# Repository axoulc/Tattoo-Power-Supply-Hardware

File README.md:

# Tattoo Power Supply Hardware

This is an open source project for a tattoo power supply circuit board. The circuit board is designed to provide power to tattoo machines, allowing artists to control the voltage and frequency of their machines for precise and consistent results.

# Features

- Dual channel power supply
- Each channel can provide up to 20V and 3A
- 1 footswitch input and 1 handswitch input
- Adjustable voltage and frequency controls
- Compatible with most tattoo machines
- OLED display for easy monitoring of voltage and frequency
- Overload protection for safety
- USB-C Power Delivery up to 100W
- DC Jack input up to 24V

# Getting Started

## PCB

To get started with this project, you will need at least KiCAD 7. You can download KiCAD from the [KiCAD website](https://kicad.org/). You will find gerber files in each release, which you can use to order PCBs from a PCB manufacturer. Every files will be available in the PCB folder. For components, you can use the BOM file to order them from a distributor `Tattoo_Supply_bom_Vx.x.csv`.

## Case

The case is designed with FreeCAD. In `Case` folder, you will find `.FCStd` files which are source files for FreeCAD and `.3mf` files which are 3D printer ready. The shapes of the case are very simple, if you're 3D designer, make it prettier !

# License

This project is licensed under the CERN Open Hardware Licence Version 2 - Permissive. See the LICENSE file for more information.

# Contact

If you have any questions or feedback about this project, please feel free to contact the project maintainer in issue section.

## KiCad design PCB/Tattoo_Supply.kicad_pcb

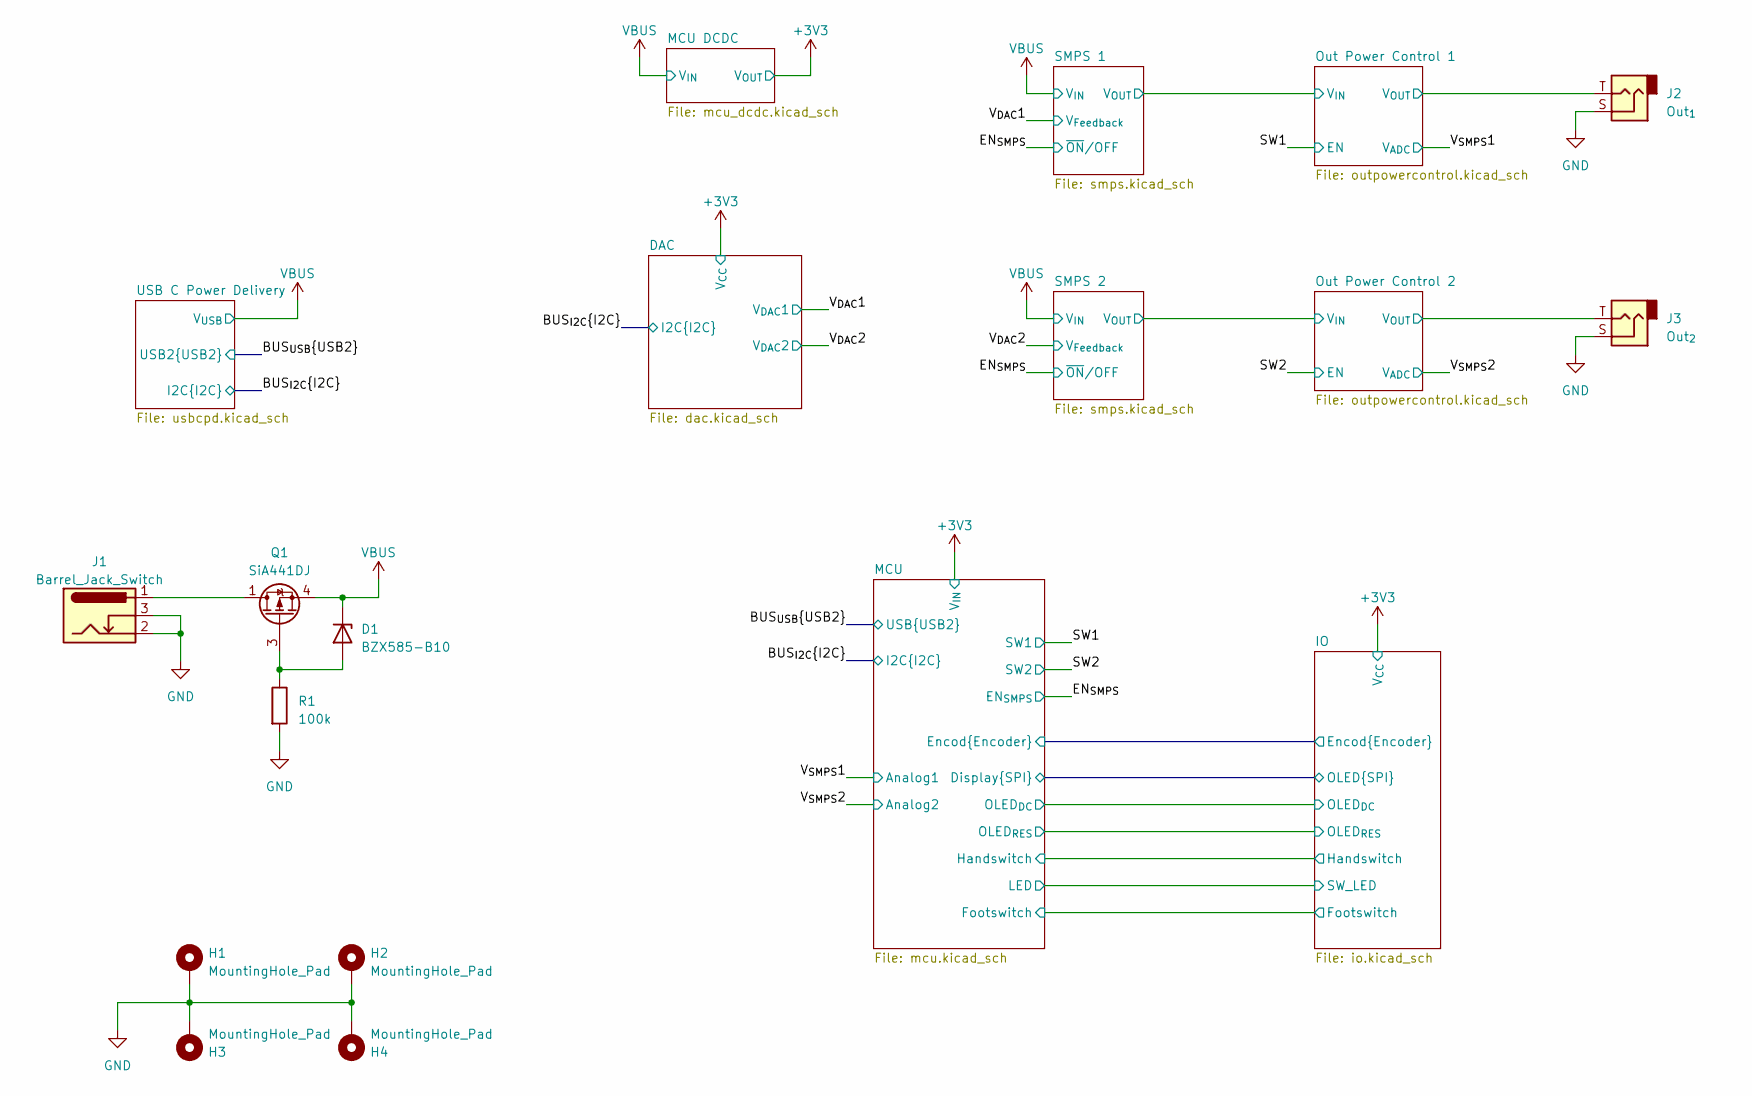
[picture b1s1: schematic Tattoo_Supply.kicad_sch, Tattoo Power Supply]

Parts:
D1: BZX585-B10; D_SOD-523; MPN BZX585-B10,135
H1, H2, H3, H4: MountingHole_Pad; MountingHole_2.7mm_M2.5_DIN965_Pad
J1: Barrel_Jack_Switch; BarrelJack_CUI_PJ-102AH_Horizontal; MPN PJ-102A
J2: Out_{1}; MJ63022A; MPN MJ-63022A
J3: Out_{2}; MJ63022A; MPN MJ-63022A
Q1: SiA441DJ; Vishay_PowerPAK_SC70-6L_Single; MPN SIA441DJ-T1-GE3
R1: 100k; R_0603_1608Metric; MPN ERJ-3EKF1003V

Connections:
/Out Power Control 1/V_{OUT}: J2.T; also elsewhere on the board
/Out Power Control 2/V_{OUT}: J3.T; also elsewhere on the board
GND: H1.1, H2.1, H3.1, H4.1, J1.2, J1.3, J2.S, J3.S, R1.2; also elsewhere on the board
unnamed: D1.2 (A), Q1.3 (G), R1.1
unnamed: J1.1, Q1.1 (D)
VBUS: D1.1 (K), Q1.4 (S); also elsewhere on the board

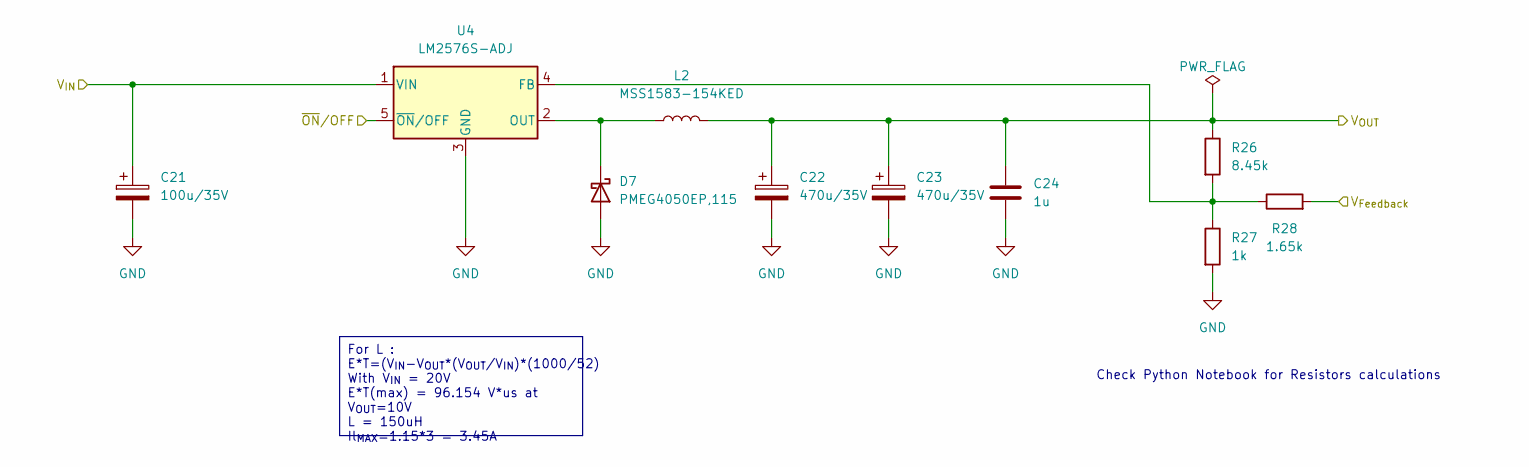
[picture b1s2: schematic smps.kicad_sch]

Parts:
C21: 100u/35V; CP_Elec_6.3x7.7; MPN 865080545012
C22, C23: 470u/35V; CP_Elec_8x10; MPN EMZS350ARA471MHA0G
C24: 1u; C_0603_1608Metric; MPN CGA3E1X7R1V105K080AC
D7: PMEG4050EP,115; D_SOD-128; MPN PMEG4050EP,115
L2: MSS1583-154KED; MSS1583; MPN MSS1583-154KED
R26: 8.45k; R_0603_1608Metric; MPN ERJ-3EKF8451V
R27: 1k; R_0603_1608Metric; MPN ERJ-3EKF1001V
R28: 1.65k; R_0603_1608Metric; MPN ERJ-3EKF1651V
U4: LM2576S-ADJ; TO-263-5_TabPin3; MPN LM2576D2T-ADJR4G

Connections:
/EN_{SMPS}: U4.5 (~ON/OFF); also elsewhere on the board
/Out Power Control 1/V_{IN}: C22.1, C23.1, C24.1, L2.2, R26.1; also elsewhere on the board
/V_{DAC}1: R28.2; also elsewhere on the board
GND: C21.2, C22.2, C23.2, C24.2, D7.2 (A), R27.2, U4.3 (GND); also elsewhere on the board
unnamed: D7.1 (K), L2.1, U4.2 (OUT)
unnamed: R26.2, R27.1, R28.1, U4.4 (FB)
VBUS: C21.1, U4.1 (VIN); also elsewhere on the board

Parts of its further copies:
C7: 100u/35V; CP_Elec_6.3x7.7; MPN 865080545012
C8, C9: 470u/35V; CP_Elec_8x10; MPN EMZS350ARA471MHA0G
C10: 1u; C_0603_1608Metric; MPN CGA3E1X7R1V105K080AC
D6: PMEG4050EP,115; D_SOD-128; MPN PMEG4050EP,115
L1: MSS1583-154KED; MSS1583; MPN MSS1583-154KED
R13: 8.45k; R_0603_1608Metric; MPN ERJ-3EKF8451V
R14: 1k; R_0603_1608Metric; MPN ERJ-3EKF1001V
R15: 1.65k; R_0603_1608Metric; MPN ERJ-3EKF1651V
U2: LM2576S-ADJ; TO-263-5_TabPin3; MPN LM2576D2T-ADJR4G

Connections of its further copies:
/EN_{SMPS}: U2.5 (~ON/OFF); also elsewhere on the board
/Out Power Control 2/V_{IN}: C8.1, C9.1, C10.1, L1.2, R13.1; also elsewhere on the board
/V_{DAC}2: R15.2; also elsewhere on the board
GND: C7.2, C8.2, C9.2, C10.2, D6.2 (A), R14.2, U2.3 (GND); also elsewhere on the board
unnamed: D6.1 (K), L1.1, U2.2 (OUT)
unnamed: R13.2, R14.1, R15.1, U2.4 (FB)
VBUS: C7.1, U2.1 (VIN); also elsewhere on the board

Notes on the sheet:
For L : E*T=(V_{IN}-V_{OUT}*(V_{OUT}/V_{IN})*(1000/52) With V_{IN} = 20V E*T(max) = 96.154 V*us at V_{OUT}=10V L = 150uH Il_{MAX}=1.15*3 = 3.45A
Check Python Notebook for Resistors calculations

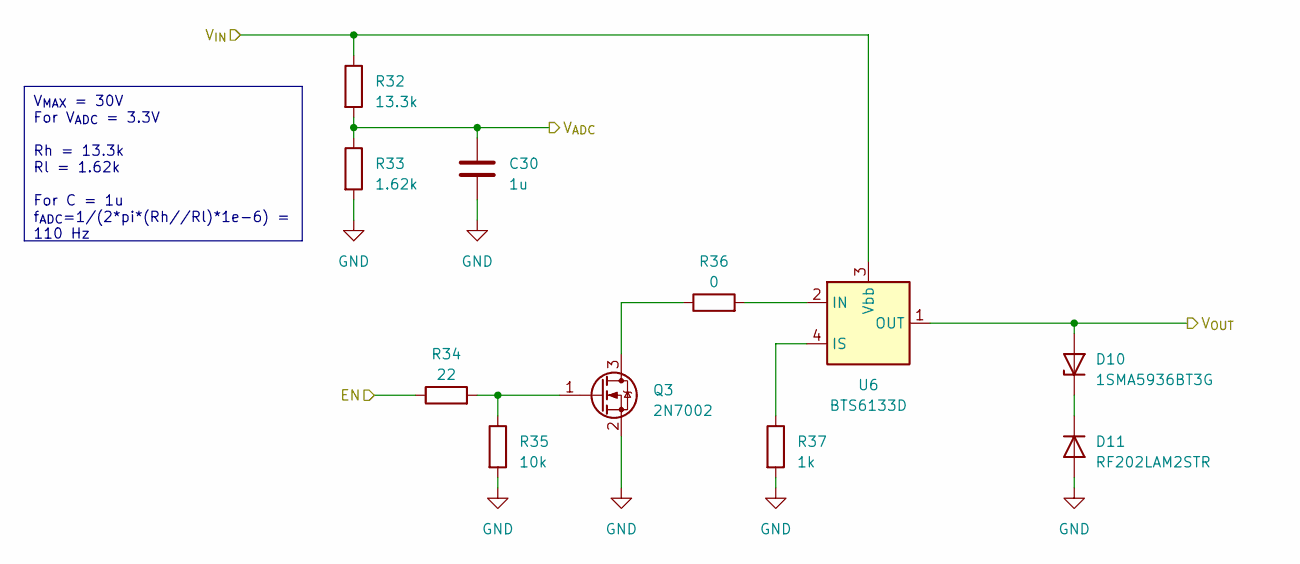
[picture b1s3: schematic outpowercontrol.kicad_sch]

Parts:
C30: 1u; C_0603_1608Metric; MPN CGA3E1X7R1V105K080AC
D10: 1SMA5936BT3G; D_SMA; MPN 1SMA5936BT3G
D11: RF202LAM2STR; D_SOD-128; MPN RF202LAM2STR
Q3: 2N7002; SOT-23; MPN 2N7002NXAKR
R32: 13.3k; R_0603_1608Metric; MPN ERJ-3EKF1332V
R33: 1.62k; R_0603_1608Metric; MPN ERJ-3EKF1621V
R34: 22; R_0603_1608Metric; MPN ERJ-3EKF22R0V
R35: 10k; R_0603_1608Metric; MPN ERJ-3EKF1002V
R36: 0; R_0603_1608Metric; MPN ERJ-3GEY0R00V
R37: 1k; R_0603_1608Metric; MPN ERJ-3EKF1001V
U6: BTS6133D; TO-252-4; MPN BTS6133D

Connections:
/Out Power Control 1/V_{IN}: R32.1, U6.3 (Vbb); also elsewhere on the board
/Out Power Control 1/V_{OUT}: D10.2 (A), U6.1 (OUT), U6.5 (OUT); also elsewhere on the board
/SW1: R34.1; also elsewhere on the board
/V_{SMPS}1: C30.1, R32.2, R33.1; also elsewhere on the board
GND: C30.2, D11.2 (A), Q3.2 (S), R33.2, R35.2, R37.2; also elsewhere on the board
unnamed: D10.1 (K), D11.1 (K)
unnamed: Q3.3 (D), R36.1
unnamed: Q3.1 (G), R34.2, R35.1
unnamed: R36.2, U6.2 (IN)
unnamed: R37.1, U6.4 (IS)

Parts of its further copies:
C34: 1u; C_0603_1608Metric; MPN CGA3E1X7R1V105K080AC
D12: 1SMA5936BT3G; D_SMA; MPN 1SMA5936BT3G
D13: RF202LAM2STR; D_SOD-128; MPN RF202LAM2STR
Q4: 2N7002; SOT-23; MPN 2N7002NXAKR
R42: 13.3k; R_0603_1608Metric; MPN ERJ-3EKF1332V
R43: 1.62k; R_0603_1608Metric; MPN ERJ-3EKF1621V
R44: 22; R_0603_1608Metric; MPN ERJ-3EKF22R0V
R45: 10k; R_0603_1608Metric; MPN ERJ-3EKF1002V
R46: 0; R_0603_1608Metric; MPN ERJ-3GEY0R00V
R47: 1k; R_0603_1608Metric; MPN ERJ-3EKF1001V
U8: BTS6133D; TO-252-4; MPN BTS6133D

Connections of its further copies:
/Out Power Control 2/V_{IN}: R42.1, U8.3 (Vbb); also elsewhere on the board
/Out Power Control 2/V_{OUT}: D12.2 (A), U8.1 (OUT), U8.5 (OUT); also elsewhere on the board
/SW2: R44.1; also elsewhere on the board
/V_{SMPS}2: C34.1, R42.2, R43.1; also elsewhere on the board
GND: C34.2, D13.2 (A), Q4.2 (S), R43.2, R45.2, R47.2; also elsewhere on the board
unnamed: D12.1 (K), D13.1 (K)
unnamed: Q4.3 (D), R46.1
unnamed: Q4.1 (G), R44.2, R45.1
unnamed: R46.2, U8.2 (IN)
unnamed: R47.1, U8.4 (IS)

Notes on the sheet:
V_{MAX} = 30V For V_{ADC} = 3.3V Rh = 13.3k Rl = 1.62k For C = 1u f_{ADC}=1/(2*pi*(Rh//Rl)*1e-6) = 110 Hz

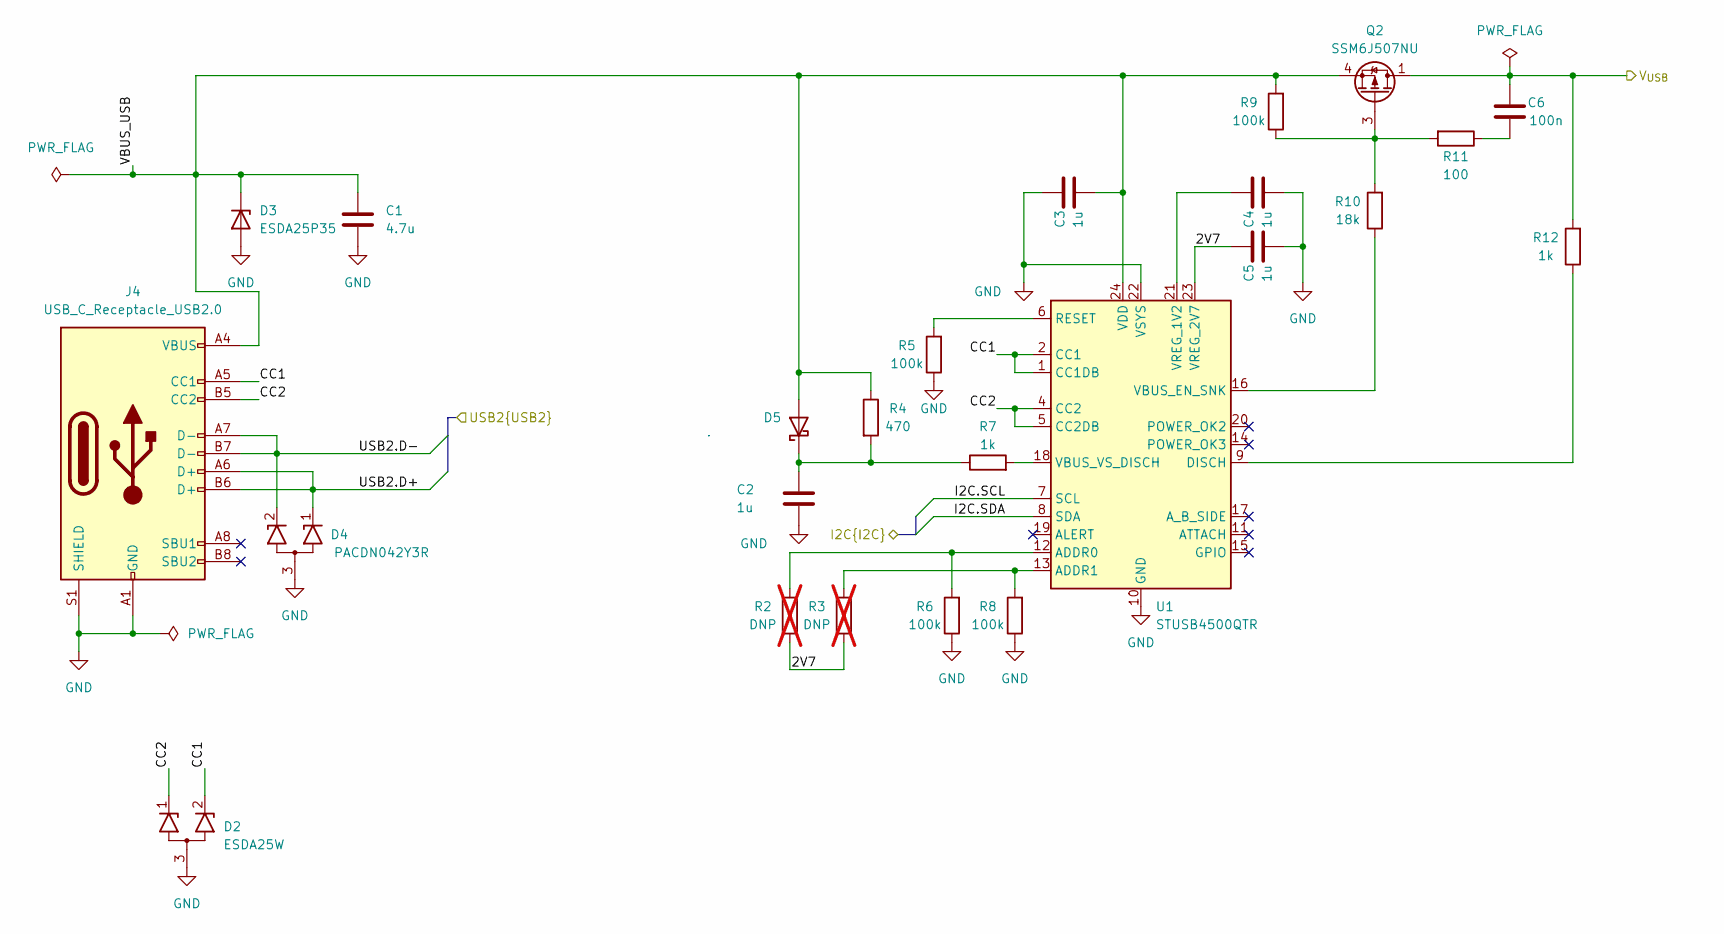
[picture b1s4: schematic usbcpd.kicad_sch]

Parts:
C1: 4.7u; C_0805_2012Metric; MPN GRM219R6YA475KA73D
C2, C3, C4, C5: 1u; C_0603_1608Metric; MPN CGA3E1X7R1V105K080AC
C6: 100n; C_0603_1608Metric; MPN CGA3E2X7R1H104M080AA
D2: ESDA25W; SOT-323_SC-70; MPN ESDA25W
D3: ESDA25P35; D_0603_1608Metric; MPN ESDA25P35-1U1M
D4: PACDN042Y3R; SOT-23-3; MPN PACDN042Y3R
D5: RB501SM-30FHT2R; D_SOD-523; MPN RB501SM-30FHT2R
J4: USB_C_Receptacle_USB2.0; MOLEX_2137160001; MPN Molex
Q2: SSM6J507NU; TRANS_SSM6J507NU,LF; MPN SSM6J507NU
R2, R3: DNP; R_0603_1608Metric; not fitted
R4: 470; R_0603_1608Metric; MPN ERJ-3EKF4700V
R5, R6, R8, R9: 100k; R_0603_1608Metric; MPN ERJ-3EKF1003V
R7, R12: 1k; R_0603_1608Metric; MPN ERJ-3EKF1001V
R10: 18k; R_0603_1608Metric; MPN ERJ-3EKF1802V
R11: 100; R_0603_1608Metric; MPN ERJ-3EKF1000V
U1: STUSB4500QTR; QFN-24-1EP_4x4mm_P0.5mm_EP2.7x2.7mm; MPN STUSB4500QTR

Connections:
/BUS_{I2C}.SCL: U1.7 (SCL); also elsewhere on the board
/BUS_{I2C}.SDA: U1.8 (SDA); also elsewhere on the board
/BUS_{USB}.D+: D4.1 (K1), J4.A6 (D+), J4.B6 (D+); also elsewhere on the board
/BUS_{USB}.D-: D4.2 (K2), J4.A7 (D-), J4.B7 (D-); also elsewhere on the board
/USB C Power Delivery/2V7: C5.1, R2.1, R3.1, U1.23 (VREG_2V7)
/USB C Power Delivery/CC1: D2.2 (K2), J4.A5 (CC1), U1.1 (CC1DB), U1.2 (CC1)
/USB C Power Delivery/CC2: D2.1 (K1), J4.B5 (CC2), U1.4 (CC2), U1.5 (CC2DB)
/USB C Power Delivery/VBUS_USB: C1.1, C3.2, D3.1 (K), D5.2 (A), J4.A4 (VBUS), J4.A9 (VBUS), J4.B4 (VBUS), J4.B9 (VBUS), Q2.4 (S), Q2.8 (S), R4.1, R9.2, U1.24 (VDD)
GND: C1.2, C2.2, C3.1, C4.2, C5.2, D2.3 (A), D3.2 (A), D4.3 (A), J4.A1 (GND), J4.A12 (GND), J4.B1 (GND), J4.B12 (GND), J4.S1 (SHIELD), R5.1, R6.1, R8.1, U1.10 (GND), U1.22 (VSYS), U1.25 (GND); also elsewhere on the board
unnamed: C6.1, R11.1
unnamed: C2.1, D5.1 (K), R4.2, R7.1
unnamed: Q2.3 (G), R9.1, R10.2, R11.2
unnamed: R2.2, R6.2, U1.12 (ADDR0)
unnamed: R3.2, R8.2, U1.13 (ADDR1)
unnamed: R12.1, U1.9 (DISCH)
unnamed: R5.2, U1.6 (RESET)
unnamed: R10.1, U1.16 (VBUS_EN_SNK)
unnamed: R7.2, U1.18 (VBUS_VS_DISCH)
unnamed: C4.1, U1.21 (VREG_1V2)
VBUS: C6.2, Q2.1 (D), Q2.2 (D), Q2.5 (D), Q2.6 (D), Q2.7 (D), R12.2; also elsewhere on the board

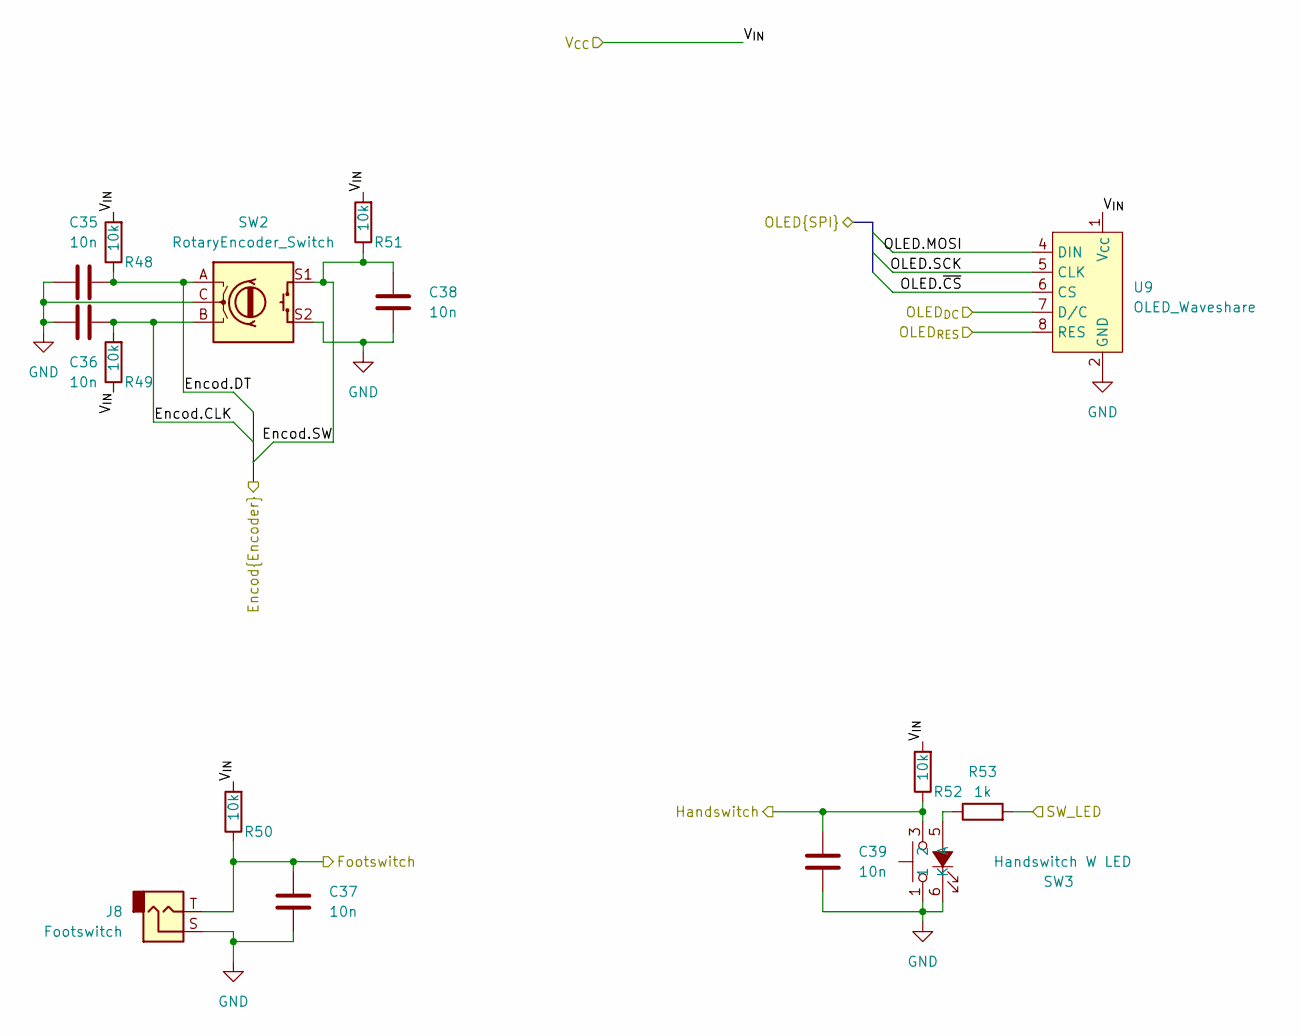
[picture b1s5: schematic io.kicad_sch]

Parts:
C35, C36, C37, C38, C39: 10n; C_0603_1608Metric; MPN GCM188R71H103KA37J
J8: Footswitch; MJ63022A; MPN MJ-63022A
R48, R49, R50, R51, R52: 10k; R_0603_1608Metric; MPN ERJ-3EKF1002V
R53: 1k; R_0603_1608Metric; MPN ERJ-3EKF1001V
SW2: RotaryEncoder_Switch; RotaryEncoder_Alps_EC11E-Switch_Vertical_H20mm; MPN PEC11R-4220F-S0024
SW3: Handswitch W LED; D6RLxx; MPN D6RLRDF1 LFS
U9: OLED_Waveshare; OLEDs_Waveshare_4SPI; MPN Waveshare

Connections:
+3V3: R48.2, R49.1, R50.2, R51.2, R52.2, U9.1 (V_{CC}); also elsewhere on the board
/IO/Encod.CLK: C36.1, R49.2, SW2.B; also elsewhere on the board
/IO/Encod.DT: C35.2, R48.1, SW2.A; also elsewhere on the board
/IO/Encod.SW: C38.1, R51.1, SW2.S1; also elsewhere on the board
/IO/Footswitch: C37.1, J8.T, R50.1; also elsewhere on the board
/IO/Handswitch: C39.1, R52.1, SW3.3 (2), SW3.4 (2); also elsewhere on the board
/IO/OLED.MOSI: U9.4 (DIN); also elsewhere on the board
/IO/OLED.SCK: U9.5 (CLK); also elsewhere on the board
/IO/OLED.~CS: U9.6 (CS); also elsewhere on the board
/IO/OLED_{DC}: U9.7 (D/C); also elsewhere on the board
/IO/OLED_{RES}: U9.8 (RES); also elsewhere on the board
/IO/SW_LED: R53.2; also elsewhere on the board
GND: C35.1, C36.2, C37.2, C38.2, C39.2, J8.S, SW2.C, SW2.S2, SW3.1, SW3.2 (1), SW3.6 (K), U9.2 (GND); also elsewhere on the board
unnamed: R53.1, SW3.5 (A)

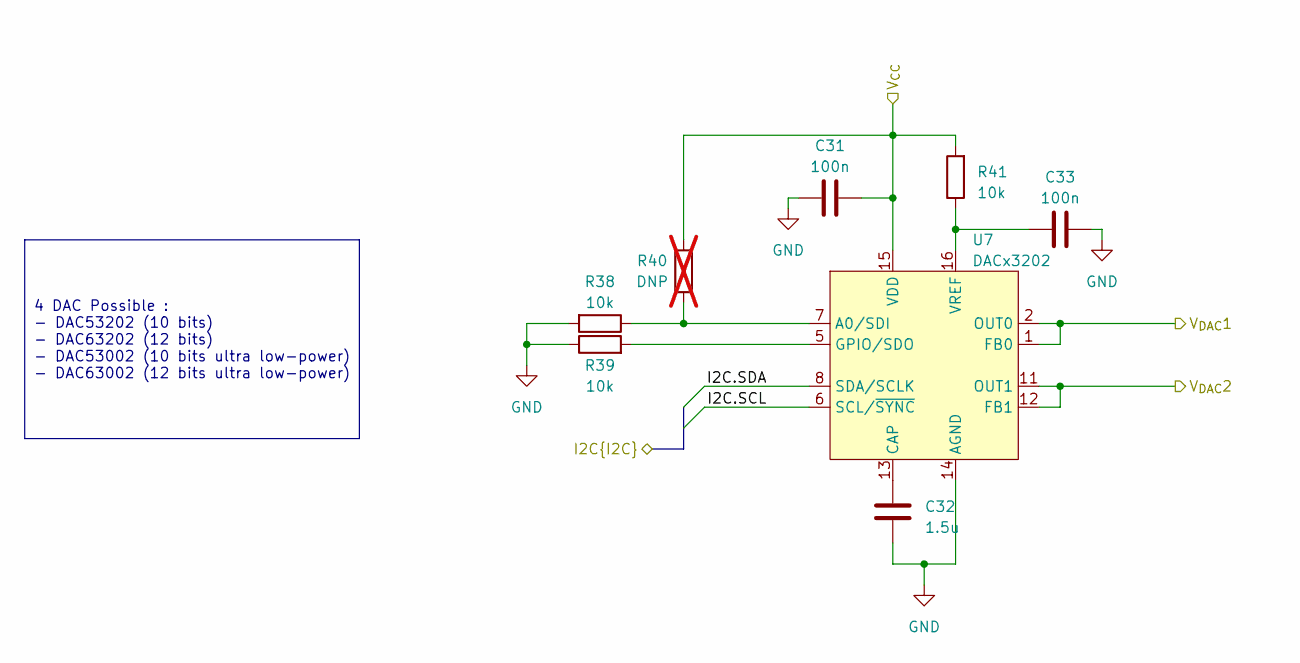
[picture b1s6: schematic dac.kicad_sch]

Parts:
C31, C33: 100n; C_0603_1608Metric; MPN CGA3E2X7R1H104M080AA
C32: 1.5u; C_0603_1608Metric; MPN C1608X7R1A155K080AC
R38, R39, R41: 10k; R_0603_1608Metric; MPN ERJ-3EKF1002V
R40: DNP; R_0603_1608Metric; not fitted
U7: DACx3202; WQFN-16-1EP_3x3mm_P0.5mm_EP1.68x1.68mm; MPN DAC63202RTER

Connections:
+3V3: C31.2, R40.2, R41.2, U7.15 (VDD); also elsewhere on the board
/BUS_{I2C}.SCL: U7.6 (SCL/~SYNC); also elsewhere on the board
/BUS_{I2C}.SDA: U7.8 (SDA/SCLK); also elsewhere on the board
/V_{DAC}1: U7.1 (FB0), U7.2 (OUT0); also elsewhere on the board
/V_{DAC}2: U7.11 (OUT1), U7.12 (FB1); also elsewhere on the board
GND: C31.1, C32.2, C33.2, R38.2, R39.1, U7.14 (AGND), U7.17 (AGND); also elsewhere on the board
unnamed: R38.1, R40.1, U7.7 (A0/SDI)
unnamed: C32.1, U7.13 (CAP)
unnamed: R39.2, U7.5 (GPIO/SDO)
unnamed: C33.1, R41.1, U7.16 (VREF)

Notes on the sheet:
4 DAC Possible : - DAC53202 (10 bits) - DAC63202 (12 bits) - DAC53002 (10 bits ultra low-power) - DAC63002 (12 bits ultra low-power)

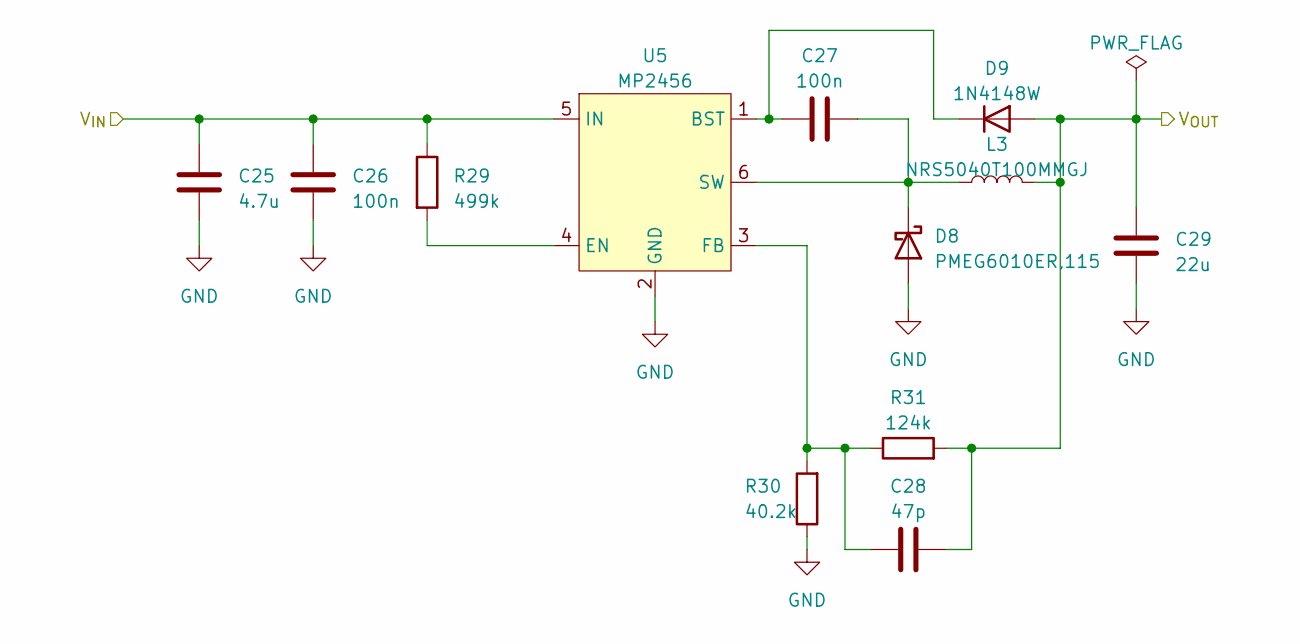
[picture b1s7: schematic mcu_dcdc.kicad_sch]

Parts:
C25: 4.7u; C_0805_2012Metric; MPN GRM219R6YA475KA73D
C26, C27: 100n; C_0603_1608Metric; MPN CGA3E2X7R1H104M080AA
C28: 47p; C_0603_1608Metric; MPN C1608C0G1H470J080AA
C29: 22u; C_0805_2012Metric; MPN GRM21BC81C226ME44L
D8: PMEG6010ER,115; D_SOD-123F; MPN PMEG6010ER,115
D9: 1N4148W; D_SOD-123; MPN 1N4148W-7-F
L3: NRS5040T100MMGJ; L_Taiyo-Yuden_NR-50xx; MPN NRS5040T100MMGJ
R29: 499k; R_0603_1608Metric; MPN ERJ-3EKF4993V
R30: 40.2k; R_0603_1608Metric; MPN ERJ-3EKF4022V
R31: 124k; R_0603_1608Metric; MPN ERJ-3EKF1243V
U5: MP2456; TSOT-23-6; MPN MP2456GJ-Z

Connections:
+3V3: C28.2, C29.1, D9.2 (A), L3.2, R31.2; also elsewhere on the board
GND: C25.2, C26.2, C29.2, D8.2 (A), R30.1, U5.2 (GND); also elsewhere on the board
unnamed: C27.2, D8.1 (K), L3.1, U5.6 (SW)
unnamed: C27.1, D9.1 (K), U5.1 (BST)
unnamed: R29.2, U5.4 (EN)
unnamed: C28.1, R30.2, R31.1, U5.3 (FB)
VBUS: C25.1, C26.1, R29.1, U5.5 (IN); also elsewhere on the board

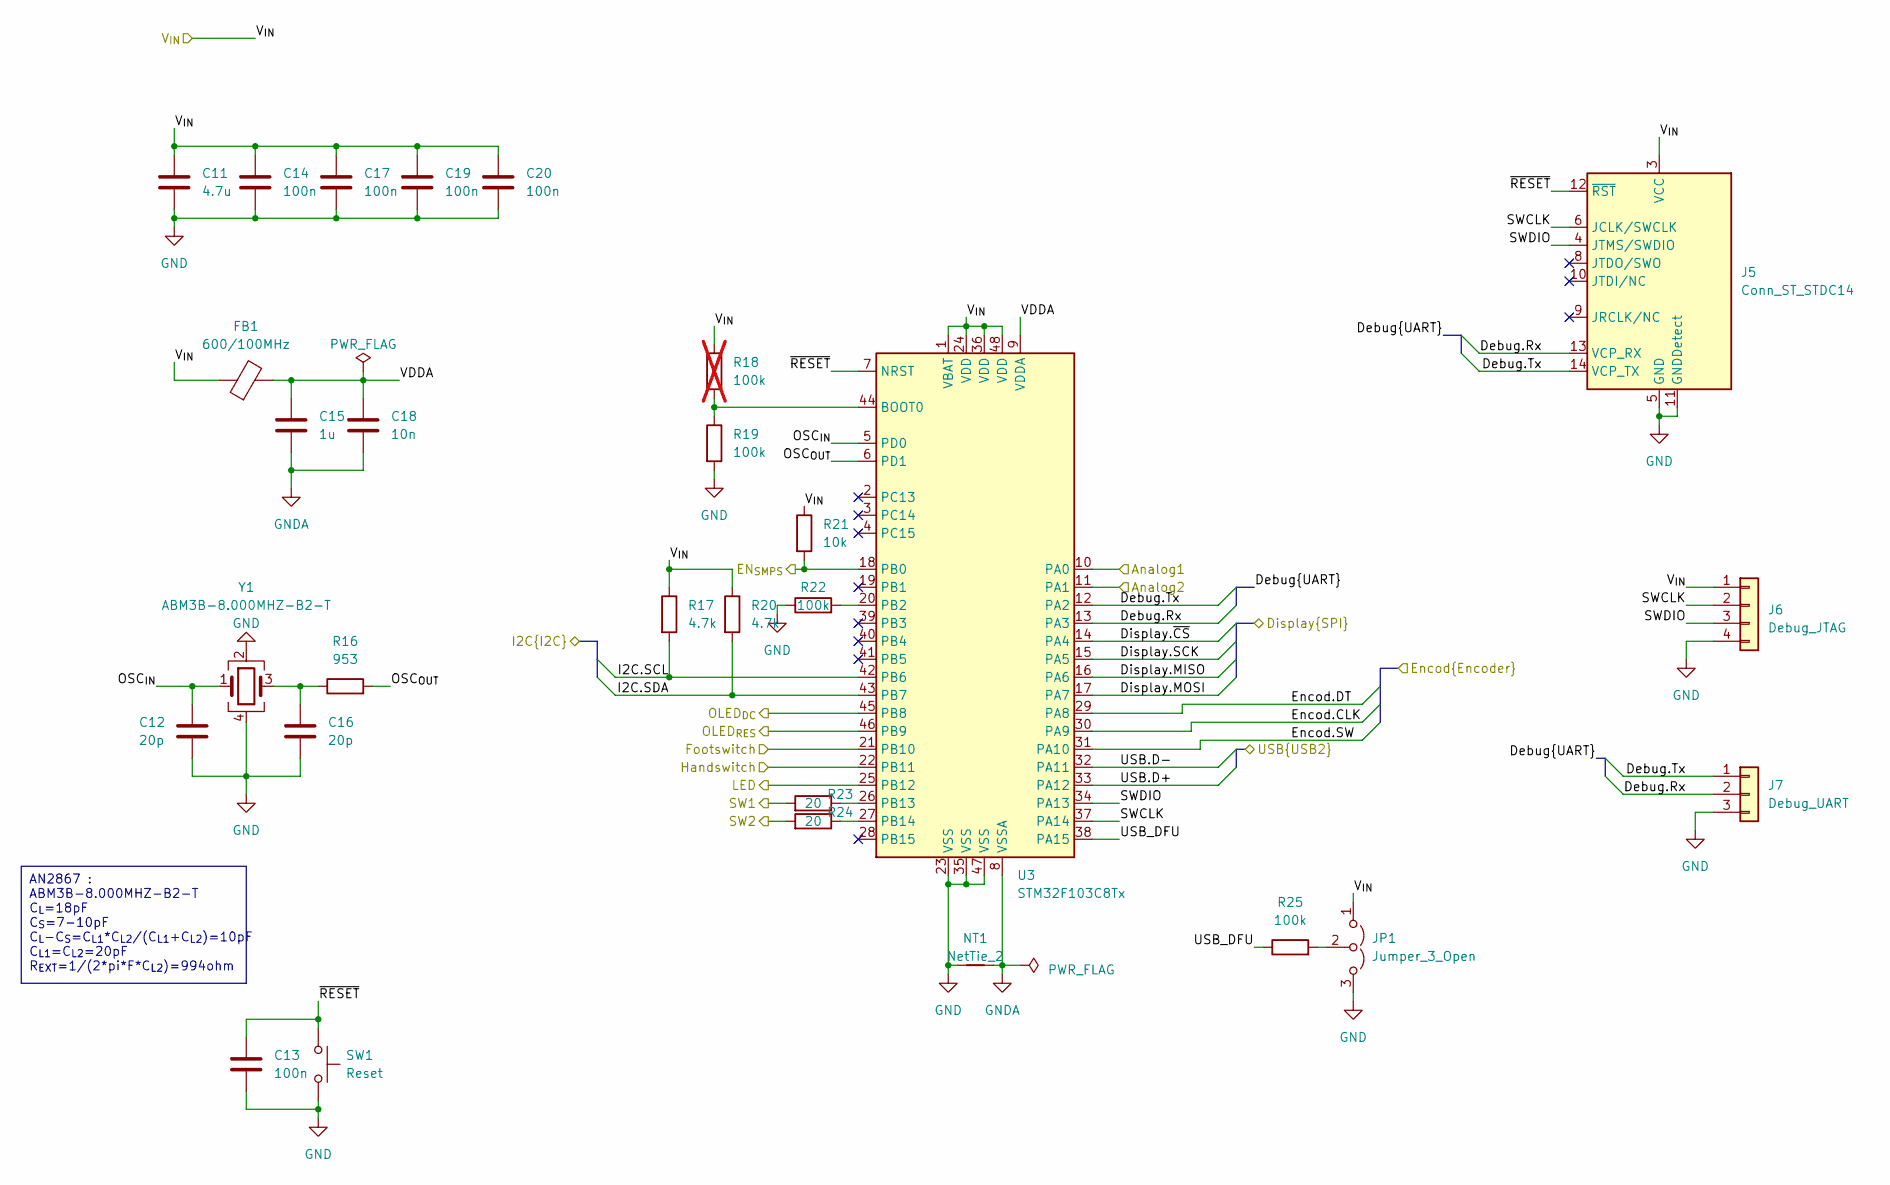
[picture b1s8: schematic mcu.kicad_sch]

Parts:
C11: 4.7u; C_0805_2012Metric; MPN GRM219R6YA475KA73D
C12, C16: 20p; C_0603_1608Metric; MPN C0603C200J5HACTU
C13, C14, C17, C19, C20: 100n; C_0603_1608Metric; MPN CGA3E2X7R1H104M080AA
C15: 1u; C_0603_1608Metric; MPN CGA3E1X7R1V105K080AC
C18: 10n; C_0603_1608Metric; MPN GCM188R71H103KA37J
FB1: 600/100MHz; R_0603_1608Metric; MPN 742792651
J5: Conn_ST_STDC14; PinHeader_2x07_P1.27mm_Vertical_SMD; MPN 20021121-00014C1LF
J6: Debug_JTAG; PinHeader_1x04_P2.54mm_Vertical
J7: Debug_UART; PinHeader_1x03_P2.54mm_Vertical
JP1: Jumper_3_Open; PinHeader_1x03_P2.54mm_Vertical
NT1: NetTie_2; NetTie-2_SMD_Pad0.5mm
R16: 953; R_0603_1608Metric; MPN ERJ-3EKF9530V
R17, R20: 4.7k; R_0603_1608Metric; MPN ERJ-3EKF4701V
R18: 100k; R_0603_1608Metric; MPN ERJ-3EKF1003V; not fitted
R19, R22, R25: 100k; R_0603_1608Metric; MPN ERJ-3EKF1003V
R21: 10k; R_0603_1608Metric; MPN ERJ-3EKF1002V
R23, R24: 20; R_0603_1608Metric; MPN ERJ-3EKF20R0V
SW1: Reset; SW_SPST_EVQP2; MPN EVQ-P2602W
U3: STM32F103C8Tx; LQFP-48_7x7mm_P0.5mm; MPN STM32F103C8T6
Y1: ABM3B-8.000MHZ-B2-T; Crystal_SMD_Abracon_ABM3B-4Pin_5.0x3.2mm; MPN ABM3B-8.000MHZ-B2-T

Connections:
+3V3: C11.1, C14.1, C17.1, C19.1, C20.1, FB1.1, J5.3 (VCC), J6.1, JP1.1 (A), R17.1, R18.1, R20.1, R21.1, U3.1 (VBAT), U3.24 (VDD), U3.36 (VDD), U3.48 (VDD); also elsewhere on the board
/BUS_{I2C}.SCL: R17.2, U3.42 (PB6); also elsewhere on the board
/BUS_{I2C}.SDA: R20.2, U3.43 (PB7); also elsewhere on the board
/BUS_{USB}.D+: U3.33 (PA12); also elsewhere on the board
/BUS_{USB}.D-: U3.32 (PA11); also elsewhere on the board
/EN_{SMPS}: R21.2, U3.18 (PB0); also elsewhere on the board
/IO/Encod.CLK: U3.30 (PA9); also elsewhere on the board
/IO/Encod.DT: U3.29 (PA8); also elsewhere on the board
/IO/Encod.SW: U3.31 (PA10); also elsewhere on the board
/IO/Footswitch: U3.21 (PB10); also elsewhere on the board
/IO/Handswitch: U3.22 (PB11); also elsewhere on the board
/IO/OLED.MISO: U3.16 (PA6)
/IO/OLED.MOSI: U3.17 (PA7); also elsewhere on the board
/IO/OLED.SCK: U3.15 (PA5); also elsewhere on the board
/IO/OLED.~CS: U3.14 (PA4); also elsewhere on the board
/IO/OLED_{DC}: U3.45 (PB8); also elsewhere on the board
/IO/OLED_{RES}: U3.46 (PB9); also elsewhere on the board
/IO/SW_LED: U3.25 (PB12); also elsewhere on the board
/MCU/Debug.Rx: J5.13 (VCP_RX), J7.2, U3.13 (PA3)
/MCU/Debug.Tx: J5.14 (VCP_TX), J7.1, U3.12 (PA2)
/MCU/OSC_{IN}: C12.1, U3.5 (PD0), Y1.1
/MCU/OSC_{OUT}: R16.2, U3.6 (PD1)
/MCU/SWCLK: J5.6 (JCLK/SWCLK), J6.2, U3.37 (PA14)
/MCU/SWDIO: J5.4 (JTMS/SWDIO), J6.3, U3.34 (PA13)
/MCU/USB_DFU: R25.1, U3.38 (PA15)
/MCU/VDDA: C15.1, C18.1, FB1.2, U3.9 (VDDA)
/MCU/~RESET: C13.1, J5.12 (~RST), SW1.1, U3.7 (NRST)
/SW1: R23.2; also elsewhere on the board
/SW2: R24.2; also elsewhere on the board
/V_{SMPS}1: U3.10 (PA0); also elsewhere on the board
/V_{SMPS}2: U3.11 (PA1); also elsewhere on the board
GND: C11.2, C12.2, C13.2, C14.2, C16.2, C17.2, C19.2, C20.2, J5.5 (GND), J5.7 (GND), J5.11 (GNDDetect), J6.4, J7.3, JP1.3 (B), NT1.2, R19.2, R22.1, SW1.2, U3.23 (VSS), U3.35 (VSS), U3.47 (VSS), Y1.2, Y1.4; also elsewhere on the board
GNDA: C15.2, C18.2, NT1.1, U3.8 (VSSA)
unnamed: C16.1, R16.1, Y1.3
unnamed: JP1.2 (C), R25.2
unnamed: R18.2, R19.1, U3.44 (BOOT0)
unnamed: R22.2, U3.20 (PB2)
unnamed: R23.1, U3.26 (PB13)
unnamed: R24.1, U3.27 (PB14)

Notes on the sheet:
AN2867 : ABM3B-8.000MHZ-B2-T C_{L}=18pF C_{S}=7-10pF C_{L}-C_{S}=C_{L1}*C_{L2}/(C_{L1}+C_{L2})=10pF C_{L1}=C_{L2}=20pF R_{EXT}=1/(2*pi*F*C_{L2})=994ohm

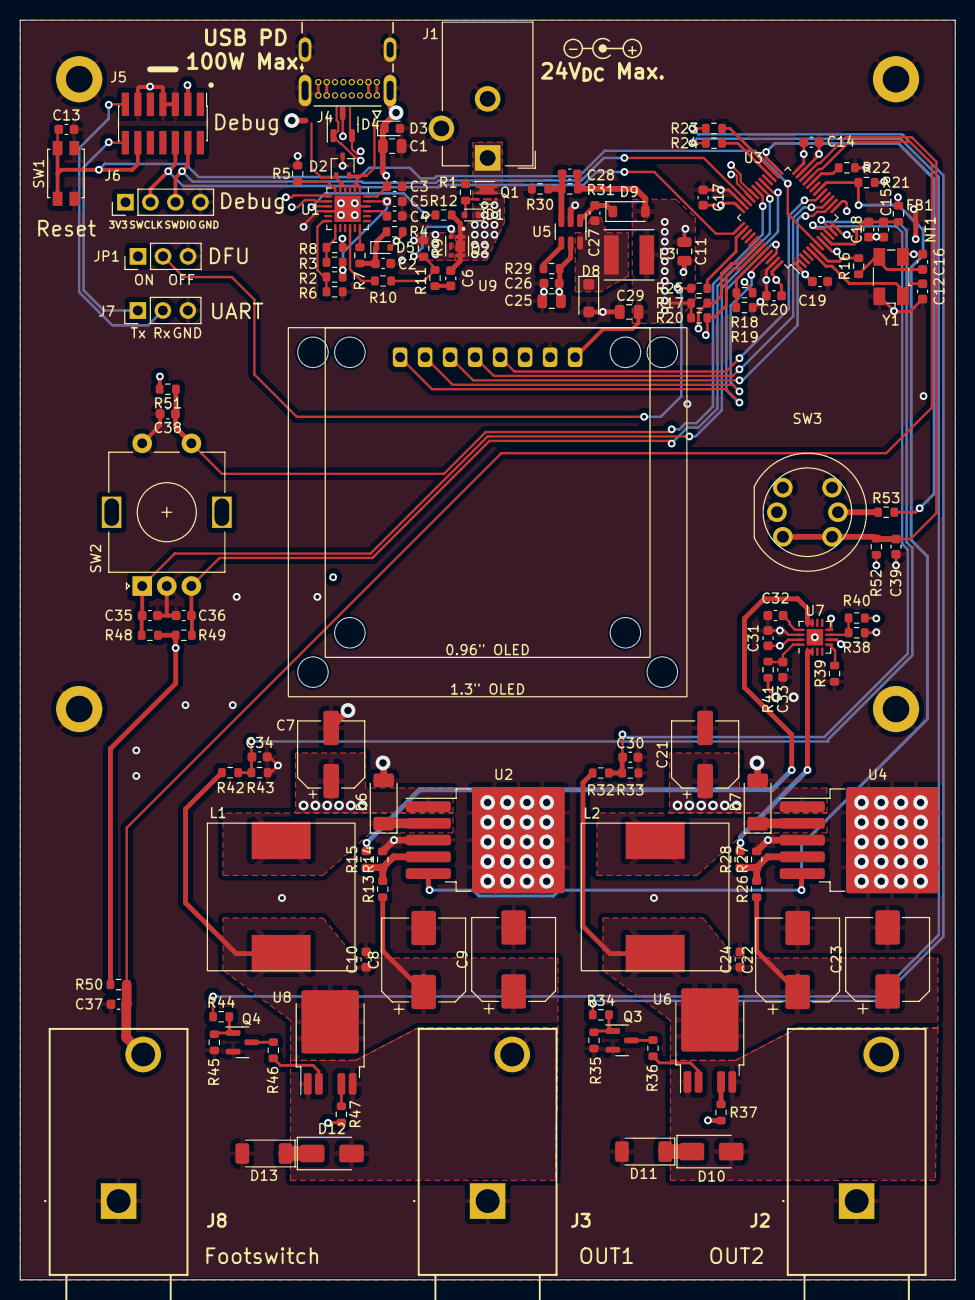
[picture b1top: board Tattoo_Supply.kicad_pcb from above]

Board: 4 copper layers, 95.0 x 128.0 mm, 140 parts (0 on the bottom side), 84 nets.

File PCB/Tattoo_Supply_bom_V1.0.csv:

References,Value,Footprint,Quantity Per PCB,Manufacturer,MPN,Alt Manufacturer,Alt MPN
C12 C16,20p,C_0603_1608Metric,2,Kemet,C0603C200J5HACTU,,
C28,47p,C_0603_1608Metric,1,TDK,C1608C0G1H470J080AA,,
C18 C35 C36 C37 C38 C39,10n,C_0603_1608Metric,6,Murata,GCM188R71H103KA37J,,
C6 C13 C14 C17 C19 C20 C26 C27 C31 C33,100n,C_0603_1608Metric,10,TDK,CGA3E2X7R1H104M080AA,,
C2 C3 C4 C5 C10 C15 C24 C30 C34,1u,C_0603_1608Metric,9,TDK,CGA3E1X7R1V105K080AC,,
C32,1.5u,C_0603_1608Metric,1,TDK,C1608X7R1A155K080AC,,
C1 C11 C25,4.7u,C_0805_2012Metric,3,Murata,GRM219R6YA475KA73D,,
C29,22u,C_0805_2012Metric,1,Murata,GRM21BC81C226ME44L,,
C7 C21,100u/35V,CP_Elec_6.3x7.7,2,Wurth Elektronik,865080545012,,
C8 C9 C22 C23,470u/35V,CP_Elec_8x10,4,United Chemi-Con ,EMZS350ARA471MHA0G,,
D9,1N4148W,D_SOD-123,1,Diodes Incorporated,1N4148W-7-F,,
D10 D12,1SMA5936BT3G,D_SMA,2,Onsemi,1SMA5936BT3G,,
D1,BZX585-B10,D_SOD-523,1,Nexperia,"BZX585-B10,135",,
D3,ESDA25P35,D_0603_1608Metric,1,STMicroelectronics,ESDA25P35-1U1M,,
D2,ESDA25W,SOT-323_SC-70,1,STMicroelectronics,ESDA25W,,
D4,PACDN042Y3R,SOT-23-3,1,Onsemi,PACDN042Y3R,,
D6 D7,"PMEG4050EP,115",D_SOD-128,2,Nexperia,"PMEG4050EP,115",,
D8,"PMEG6010ER,115",D_SOD-123F,1,Nexperia,"PMEG6010ER,115",,
D5,RB501SM-30FHT2R,D_SOD-523,1,ROHM,RB501SM-30FHT2R,,
D11 D13,RF202LAM2STR,D_SOD-128,2,ROHM,RF202LAM2STR,,
FB1,600/100MHz,R_0603_1608Metric,1,Wurth Elektronik,742792651,,
J1,Barrel_Jack_Switch,BarrelJack_CUI_PJ-102AH_Horizontal,1,CUI Devices,PJ-102A,,
J5,Conn_ST_STDC14,PinSocket_2x07_P1.27mm_Vertical_SMD,1,Amphenol FCI,20021121-00014C1LF,,
J2 J3 J8,Out_{1} Out_{2} Footswitch,MJ63022A,3,CUI Devices,MJ-63022A,,
J4,USB_C_Receptacle_USB2.0,USB_C_Receptacle_GCT_USB4105-xx-A_16P_TopMnt_Horizontal,1,GCT,USB4105-GF-A,,
L1 L2,MSS1583-154KED,MSS1583,2,Coilcraft,MSS1583-154KED,,
L3,NRS5040T100MMGJ,L_Taiyo-Yuden_NR-50xx,1,Taiyo Yuden,NRS5040T100MMGJ,,
Q3 Q4,2N7002,SOT-23,2,Nexperia,2N7002NXAKR,,
Q2,SSM6J507NU,"TRANS_SSM6J507NU,LF",1,Toshiba,"SSM6J507NU,LF",,
Q1,SiA441DJ,Vishay_PowerPAK_SC70-6L_Single,1,Vishay Semiconductors,SIA441DJ-T1-GE3,,
R36 R46,0,R_0603_1608Metric,2,Panasonic,ERJ-3GEY0R00V,,
R23 R24,20,R_0603_1608Metric,2,Panasonic,ERJ-3EKF20R0V,,
R34 R44,22,R_0603_1608Metric,2,Panasonic,ERJ-3EKF22R0V,,
R11,100,R_0603_1608Metric,1,Panasonic,ERJ-3EKF1000V,,
R4,470,R_0603_1608Metric,1,Panasonic,ERJ-3EKF4700V,,
R16,953,R_0603_1608Metric,1,Panasonic,ERJ-3EKF9530V,,
R7 R12 R14 R27 R37 R47 R53,1k,R_0603_1608Metric,7,Panasonic,ERJ-3EKF1001V,,
R33 R43,1.62k,R_0603_1608Metric,2,Panasonic,ERJ-3EKF1621V,,
R15 R28,1.65k,R_0603_1608Metric,2,Panasonic,ERJ-3EKF1651V,,
R17 R20,4.7k,R_0603_1608Metric,2,Panasonic,ERJ-3EKF4701V,,
R13 R26,8.45k,R_0603_1608Metric,2,Panasonic,ERJ-3EKF8451V,,
R21 R35 R38 R39 R41 R45 R48 R49 R50 R51 R52,10k,R_0603_1608Metric,11,Panasonic,ERJ-3EKF1002V,,
R32 R42,13.3k,R_0603_1608Metric,2,Panasonic,ERJ-3EKF1332V,,
R10,18k,R_0603_1608Metric,1,Panasonic,ERJ-3EKF1802V,,
R30,40.2k,R_0603_1608Metric,1,Panasonic,ERJ-3EKF4022V,,
R1 R5 R6 R8 R9 R18 R19 R22 R25,100k,R_0603_1608Metric,9,Panasonic,ERJ-3EKF1003V,,
R31,124k,R_0603_1608Metric,1,Panasonic,ERJ-3EKF1243V,,
R29,499k,R_0603_1608Metric,1,Panasonic,ERJ-3EKF4993V,,
SW3,Handswitch W LED,D6RLxx,1,C&K,D6RLRDF1 LFS,,
SW1,Reset,SW_SPST_EVQP2,1,Panasonic,EVQ-P2602W,,
SW2,RotaryEncoder_Switch,RotaryEncoder_Alps_EC11E-Switch_Vertical_H20mm,1,Bourns,PEC11R-4220F-S0024,,
U6 U8,BTS6133D,TO-252-4,2,Infineon,BTS6133D,,
U7,DACx3202,WQFN-16-1EP_3x3mm_P0.5mm_EP1.68x1.68mm,1,Texas Instruments,DAC63202RTER,,
U2 U4,LM2576S-ADJ,TO-263-5_TabPin3,2,Onsemi,LM2576D2T-ADJR4G,,
U5,MP2456,TSOT-23-6,1,Monolithic Power Systems,MP2456GJ-Z,,
U9,OLED_Waveshare,OLEDs_Waveshare_4SPI,1,10451,Waveshare,Waveshare,9092
U3,STM32F103C8Tx,LQFP-48_7x7mm_P0.5mm,1,STMicroelectronics,STM32F103C8T6,,
U1,STUSB4500QTR,QFN-24-1EP_4x4mm_P0.5mm_EP2.7x2.7mm,1,STMicroelectronics,STUSB4500QTR,,
Y1,ABM3B-8.000MHZ-B2-T,Crystal_SMD_Abracon_ABM3B-4Pin_5.0x3.2mm,1,Abracon,ABM3B-8.000MHZ-B2-T,,
